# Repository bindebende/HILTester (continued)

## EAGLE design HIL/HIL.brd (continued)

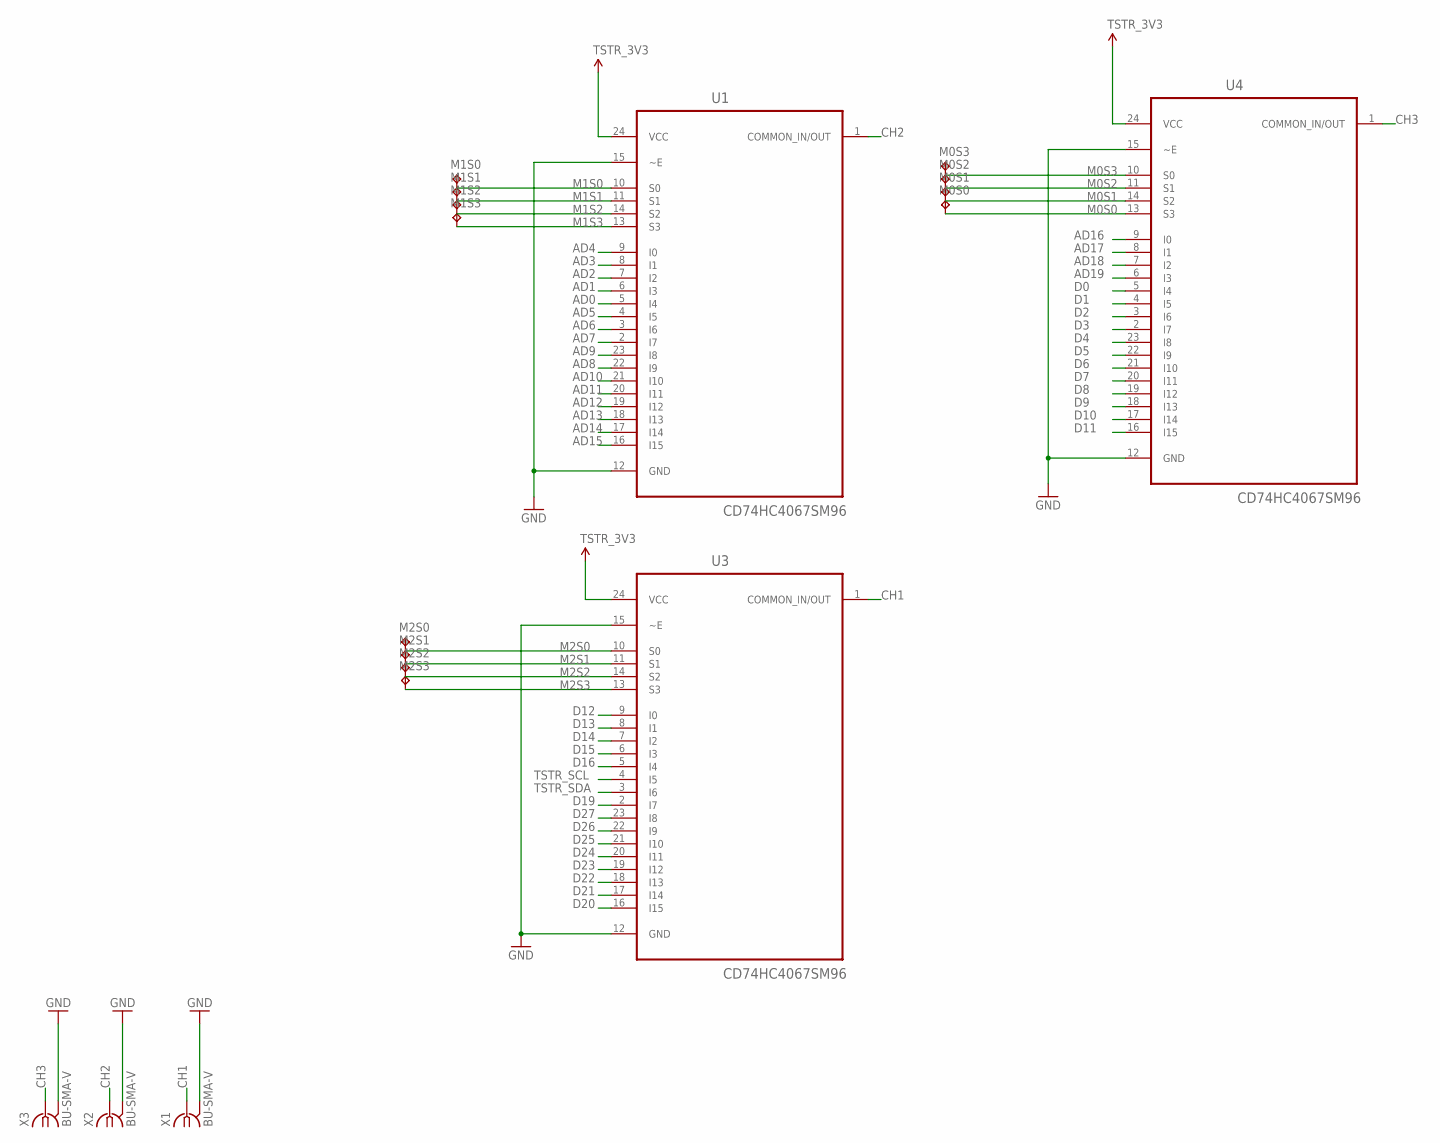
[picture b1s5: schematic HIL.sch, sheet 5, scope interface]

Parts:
M0S0, M0S1, M0S2, M0S3: TPB1,27; B1,27
M1S0, M1S1, M1S2, M1S3, M2S0, M2S1, M2S2, M2S3: M0S3; B1,27
U1, U3, U4: CD74HC4067SM96; SOP65P780X200-24N
X1, X2, X3: BU-SMA-V

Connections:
AD0: U1.5 (I4); also elsewhere on the board
AD1: U1.6 (I3); also elsewhere on the board
AD2: U1.7 (I2); also elsewhere on the board
AD3: U1.8 (I1); also elsewhere on the board
AD4: U1.9 (I0); also elsewhere on the board
AD5: U1.4 (I5); also elsewhere on the board
AD6: U1.3 (I6); also elsewhere on the board
AD7: U1.2 (I7); also elsewhere on the board
AD8: U1.22 (I9); also elsewhere on the board
AD9: U1.23 (I8); also elsewhere on the board
AD10: U1.21 (I10); also elsewhere on the board
AD11: U1.20 (I11); also elsewhere on the board
AD12: U1.19 (I12); also elsewhere on the board
AD13: U1.18 (I13); also elsewhere on the board
AD14: U1.17 (I14); also elsewhere on the board
AD15: U1.16 (I15); also elsewhere on the board
AD16: U4.9 (I0); also elsewhere on the board
AD17: U4.8 (I1); also elsewhere on the board
AD18: U4.7 (I2); also elsewhere on the board
AD19: U4.6 (I3); also elsewhere on the board
CH1: U3.1 (COMMON_IN/OUT), X1.1
CH2: U1.1 (COMMON_IN/OUT), X2.1
CH3: U4.1 (COMMON_IN/OUT), X3.1
D0: U4.5 (I4); also elsewhere on the board
D1: U4.4 (I5); also elsewhere on the board
D2: U4.3 (I6); also elsewhere on the board
D3: U4.2 (I7); also elsewhere on the board
D4: U4.23 (I8); also elsewhere on the board
D5: U4.22 (I9); also elsewhere on the board
D6: U4.21 (I10); also elsewhere on the board
D7: U4.20 (I11); also elsewhere on the board
D8: U4.19 (I12); also elsewhere on the board
D9: U4.18 (I13); also elsewhere on the board
D10: U4.17 (I14); also elsewhere on the board
D11: U4.16 (I15); also elsewhere on the board
D12: U3.9 (I0); also elsewhere on the board
D13: U3.8 (I1); also elsewhere on the board
D14: U3.7 (I2); also elsewhere on the board
D15: U3.6 (I3); also elsewhere on the board
D16: U3.5 (I4); also elsewhere on the board
D19: U3.2 (I7); also elsewhere on the board
D20: U3.16 (I15); also elsewhere on the board
D21: U3.17 (I14); also elsewhere on the board
D22: U3.18 (I13); also elsewhere on the board
D23: U3.19 (I12); also elsewhere on the board
D24: U3.20 (I11); also elsewhere on the board
D25: U3.21 (I10); also elsewhere on the board
D26: U3.22 (I9)
D27: U3.23 (I8)
GND: U1.12 (GND), U1.15 (~E), U3.12 (GND), U3.15 (~E), U4.12 (GND), U4.15 (~E), X1.2, X1.3 (2), X1.4 (2), X1.5 (2), X2.2, X2.3 (2), X2.4 (2), X2.5 (2), X3.2, X3.3 (2), X3.4 (2), X3.5 (2); also elsewhere on the board
M0S0: M0S0.TP, U4.13 (S3)
M0S1: M0S1.TP, U4.14 (S2)
M0S2: M0S2.TP, U4.11 (S1)
M0S3: M0S3.TP, U4.10 (S0)
M1S0: M1S0.TP, U1.10 (S0)
M1S1: M1S1.TP, U1.11 (S1)
M1S2: M1S2.TP, U1.14 (S2)
M1S3: M1S3.TP, U1.13 (S3)
M2S0: M2S0.TP, U3.10 (S0)
M2S1: M2S1.TP, U3.11 (S1)
M2S2: M2S2.TP, U3.14 (S2)
M2S3: M2S3.TP, U3.13 (S3)
TSTR_3V3: U1.24 (VCC), U3.24 (VCC), U4.24 (VCC); also elsewhere on the board
TSTR_SCL: U3.4 (I5); also elsewhere on the board
TSTR_SDA: U3.3 (I6); also elsewhere on the board

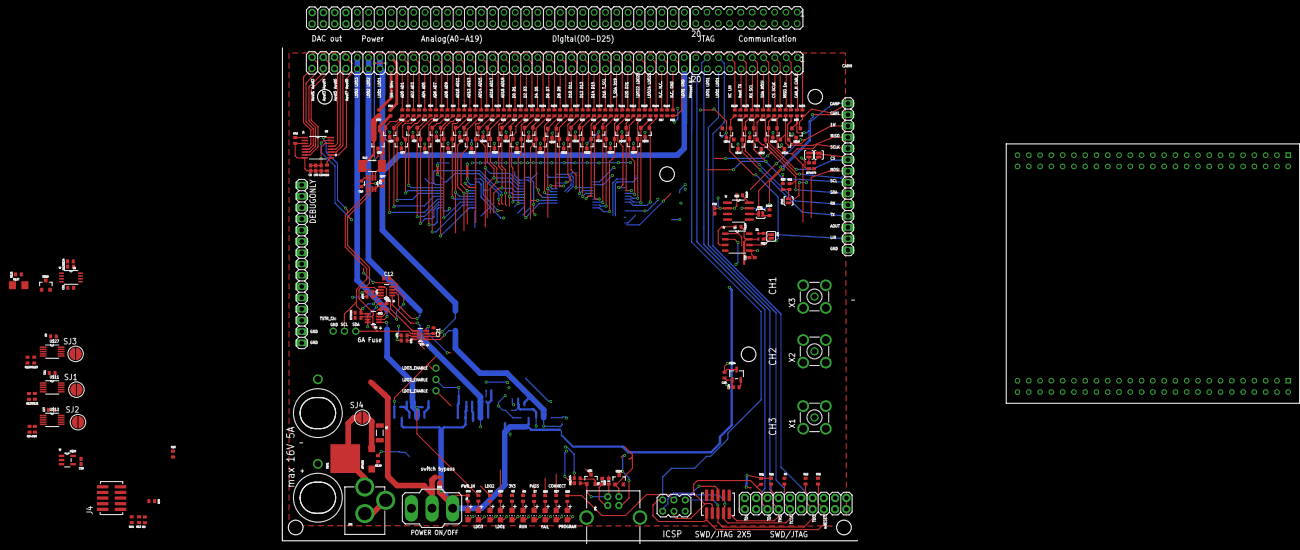
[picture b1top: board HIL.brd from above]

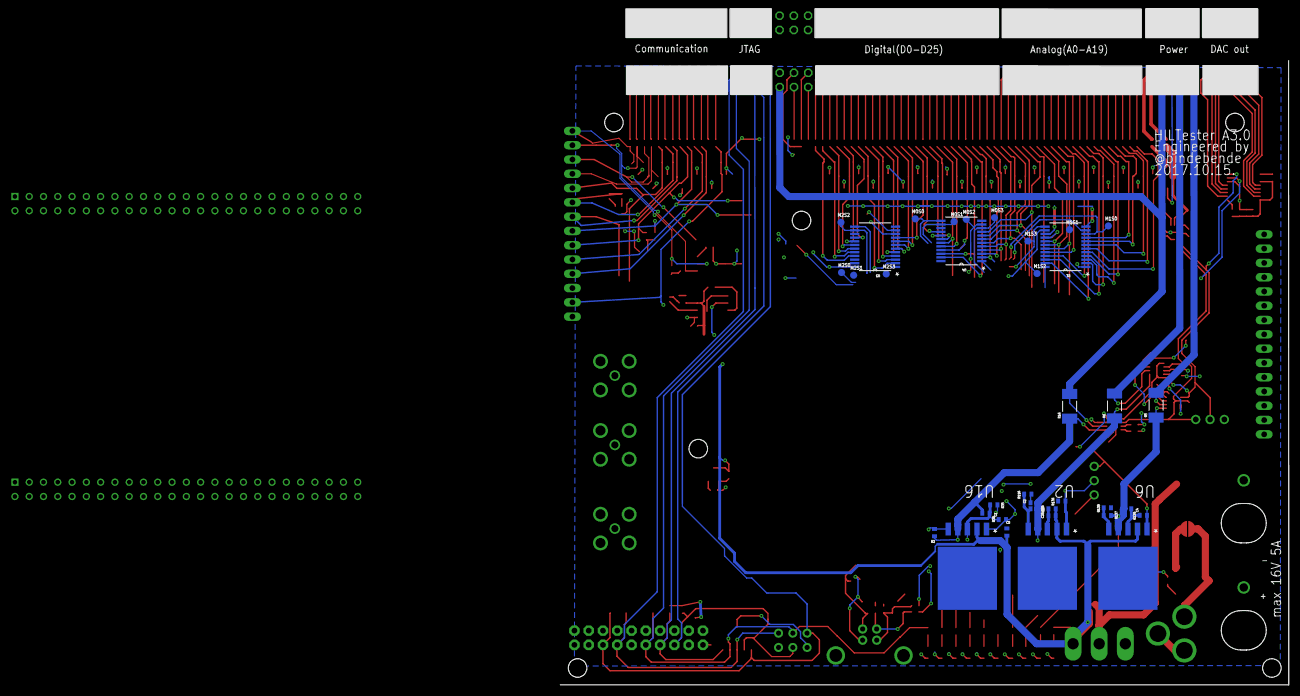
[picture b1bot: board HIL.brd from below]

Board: 2 copper layers, 129.5 x 111.0 mm, 269 parts (36 on the bottom side), 223 nets.

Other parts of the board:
STANDOFF1, STANDOFF5: STAND-OFF; STAND-OFF@1

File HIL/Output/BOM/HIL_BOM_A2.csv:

Qty;Value;Device;Package;Parts;Description
1;;320-916;320-916;S1;TOGGLE SWITCH
1;;DIODE-SOD523;SOD523;D1;DIODE
1;;GSH15;GSH15;F1;FUSE HOLDER
1;;JUMPER-2SMD-NC;SJ_2S;JP9;Jumper
1;;JUMPER-2SMD-NO;SJ_2S-NO;JP11;Jumper
10;;LEDCHIP-LED0805;CHIP-LED0805;LED1, LED2, LED3, LED4, LED5, LED6, LED7, LED8, LED9, LED10;LED
1;;MA10-2;MA10-2;SV1;PIN HEADER
1;;PINHD-1X14;1X14;JP3;PIN HEADER
1;;PINHD-1X15;1X15;DEBUGONLY;PIN HEADER
4;;PINHD-1X3CB;1X03-CLEANBIG;JP14, JP15, JP16, JP18;PIN HEADER
1;;PINHD-2X10;2X10;JP2;PIN HEADER
1;;PINHD-2X30;2X30;JP6;PIN HEADER
6;;R-EU_R0402;R0402;R2, R35, R37, R116, R137, R138;RESISTOR, European symbol
4;;R-US_R5025;R5025;R5, R6, R16, R17;RESISTOR, American symbol
4;0.1uF;C-EUC0402;C0402;C10, C12, C21, C22;CAPACITOR, European symbol
9;0.1uF;C-EUC0402K;C0402K;C3, C6, C13, C14, C16, C17, C18, C19, C20;CAPACITOR, European symbol
1;0.1uF;CC0402;C0402;C37;CAPACITOR, European symbol
3;0R;R-EU_R0402;R0402;R41, R44, R88;RESISTOR, European symbol
1;100;R-EU_R0402;R0402;R24;RESISTOR, European symbol
10;100R;R-EU_R0402;R0402;R3, R7, R8, R26, R27, R28, R29, R30, R33, R40;RESISTOR, European symbol
1;10k;R-EU_R0402;R0402;R25;RESISTOR, European symbol
6;10uF;C-EUC0402;C0402;C1, C2, C4, C5, C25, C26;CAPACITOR, European symbol
1;10uF;C-EUC0402K;C0402K;C7;CAPACITOR, European symbol
1;120;R-EU_R0402;R0402;R140;RESISTOR, European symbol
2;12pF;C-EUC0402K;C0402K;C9, C36;CAPACITOR, European symbol
1;1M;R-EU_R0402;R0402;R20;RESISTOR, European symbol
1;1k;R-EU_R0402;R0402;R117;RESISTOR, European symbol
2;1uF;C-EUC0402;C0402;C23, C24;CAPACITOR, European symbol
1;2.2uF;C-EUC0402K;C0402K;C15;CAPACITOR, European symbol
64;200R;R-EU_R0402;R0402;R39, R42, R43, R45, R47, R48, R49, R50, R51, R52, R53, R54, R55, R56, R57, R58, R59, R60, R61, R62, R63, R64, R65, R66, R67, R68, R82, R83, R84, R85, R86, R87, R91, R92, R93, R94, R95, R96, R97, R98, R99, R100, R101, R102, R103, R104, R105, R106, R107, R108, R109, R110, R111, R112, R113, R114, R115, R129, R130, R131, R132, R133, R134, R135;RESISTOR, European symbol
2;22R;RESISTOR0402-RES;0402-RES;R1, R38;Resistor
1;2k;R-EU_R0402;R0402;R23;RESISTOR, European symbol
16;4.7k;R-EU_R0402;R0402;R9, R10, R13, R14, R15, R18, R19, R34, R46, R69, R70, R71, R78, R79, R80, R81;RESISTOR, European symbol
1;4.87k 1%;R-EU_R0402;R0402;R22;RESISTOR, European symbol
16;4k7;R-EU_R0402;R0402;R4, R11, R12, R31, R32, R36, R72, R73, R74, R75, R76, R77, R118, R119, R136, R139;RESISTOR, European symbol
1;51;R-EU_R0402;R0402;R21;RESISTOR, European symbol
3;A1944-50;A1944-50;A1944;X1, X2, X4;BNC CONNECTOR 50 Ohm
1;ADUM1201ARZ;ADUM1201ARZ;SOIC127P600X175-8N;U14;Dual-Channel Digital Isolators
1;AVRISP-6;AVRISP-6;AVRISP;ISP1;AVR ISP HEADER
2;BINDING_POST;BINDING_POST;BINDING_POST;JP12, JP13;Single Banana jack.
3;CD74HC4067SM96;CD74HC4067SM96;SOP65P780X200-24N;U1, U3, U4;16-Channel Analog Multiplexer/Demultiplexer
2;DUT_CS_MASTER;JUMPER-2SMD-NO;SJ_2S-NO;JP4, JP10;Jumper
1;DUT_CS_RecieveAllMSG;JUMPER-2SMD-NO;SJ_2S-NO;JP7;Jumper
1;FT230XS;FT230XS;SOP63P600X175-16N;U17;I/F, USB2.0 FS TO BASIC UART
4;INA219AIDCNR;INA219AIDCNR;SOT65P280X145-8N;U9, U10, U11, U12;CURRENT/POWER MONITOR
2;JTAG_ARM_10PIN;JTAG_ARM_10PIN;CON_2X5_50MIL;J1, J4;
8;M0S3;TPB1,27;B1,27;M1S0, M1S1, M1S2, M1S3, M2S0, M2S1, M2S2, M2S3;Test pad
1;MCP1703T-3302E/CB;MCP1703T-3302E/CB;SOT95P300X145-3N;U$34;Low Quiescent Current LDO Regulator
1;MCP2003-E/SN;MCP2003-E/SN;SOIC127P600X175-8N;U7;LIN J2602 Transceiver,SOIC-8
1;MCP4725A0T-E/CH;MCP4725A0T-E/CH;SOT95P270X145-6N;U5;12-Bit Digital-to-Analog Converter with EEPROM
1;NX3225GA;NX3225GA;NDK3.2X2.5;Y3;
1;POWER_JACKPTH;POWER_JACKPTH;POWER_JACK_PTH;JP5;Power Jack
1;RESET;JUMPER-2SMD-NO;SJ_2S-NO;JP1;Jumper
1;SN65HVD230D;SN65HVD230D;SOIC127P600X175-8N;U15;3.3-V CAN TRANSCEIVERS
4;STAND-OFF;STAND-OFF;STAND-OFF;STANDOFF2, STANDOFF3, STANDOFF4, STANDOFF6;#4 Stand Off
1;SWS003;SWS003;SMS-003;S3;SMD Dip Switch 3 pol.
3;TL1963AKTTR.;TL1963AKTTR.;TO170P1485X457-6N;U2, U6, U16;LDO, REG, 1.5A, 1.21V TO 20V ADJ, 5TO263
1;TM4C1294NCPDT;TM4C1294NCPDT;TQFP128;U13;ARM MICROCONTROLLER
4;TPB1,27;TPB1,27;B1,27;M0S0, M0S1, M0S2, M0S3;Test pad
1;USB-B;USBPTH;USB-B-PTH;JP8;USB Connectors
33;zener_3.3V;MMBZ27VCLT1;SOT23-3;U$1, U$2, U$3, U$4, U$5, U$6, U$7, U$8, U$9, U$10, U$13, U$14, U$15, U$16, U$17, U$18, U$19, U$20, U$21, U$22, U$23, U$24, U$25, U$26, U$36, U$37, U$44, U$45, U$46, U$47, U$48, U$49, U$50;40W Zener-diode transient voltage suppressor (ESD protection)

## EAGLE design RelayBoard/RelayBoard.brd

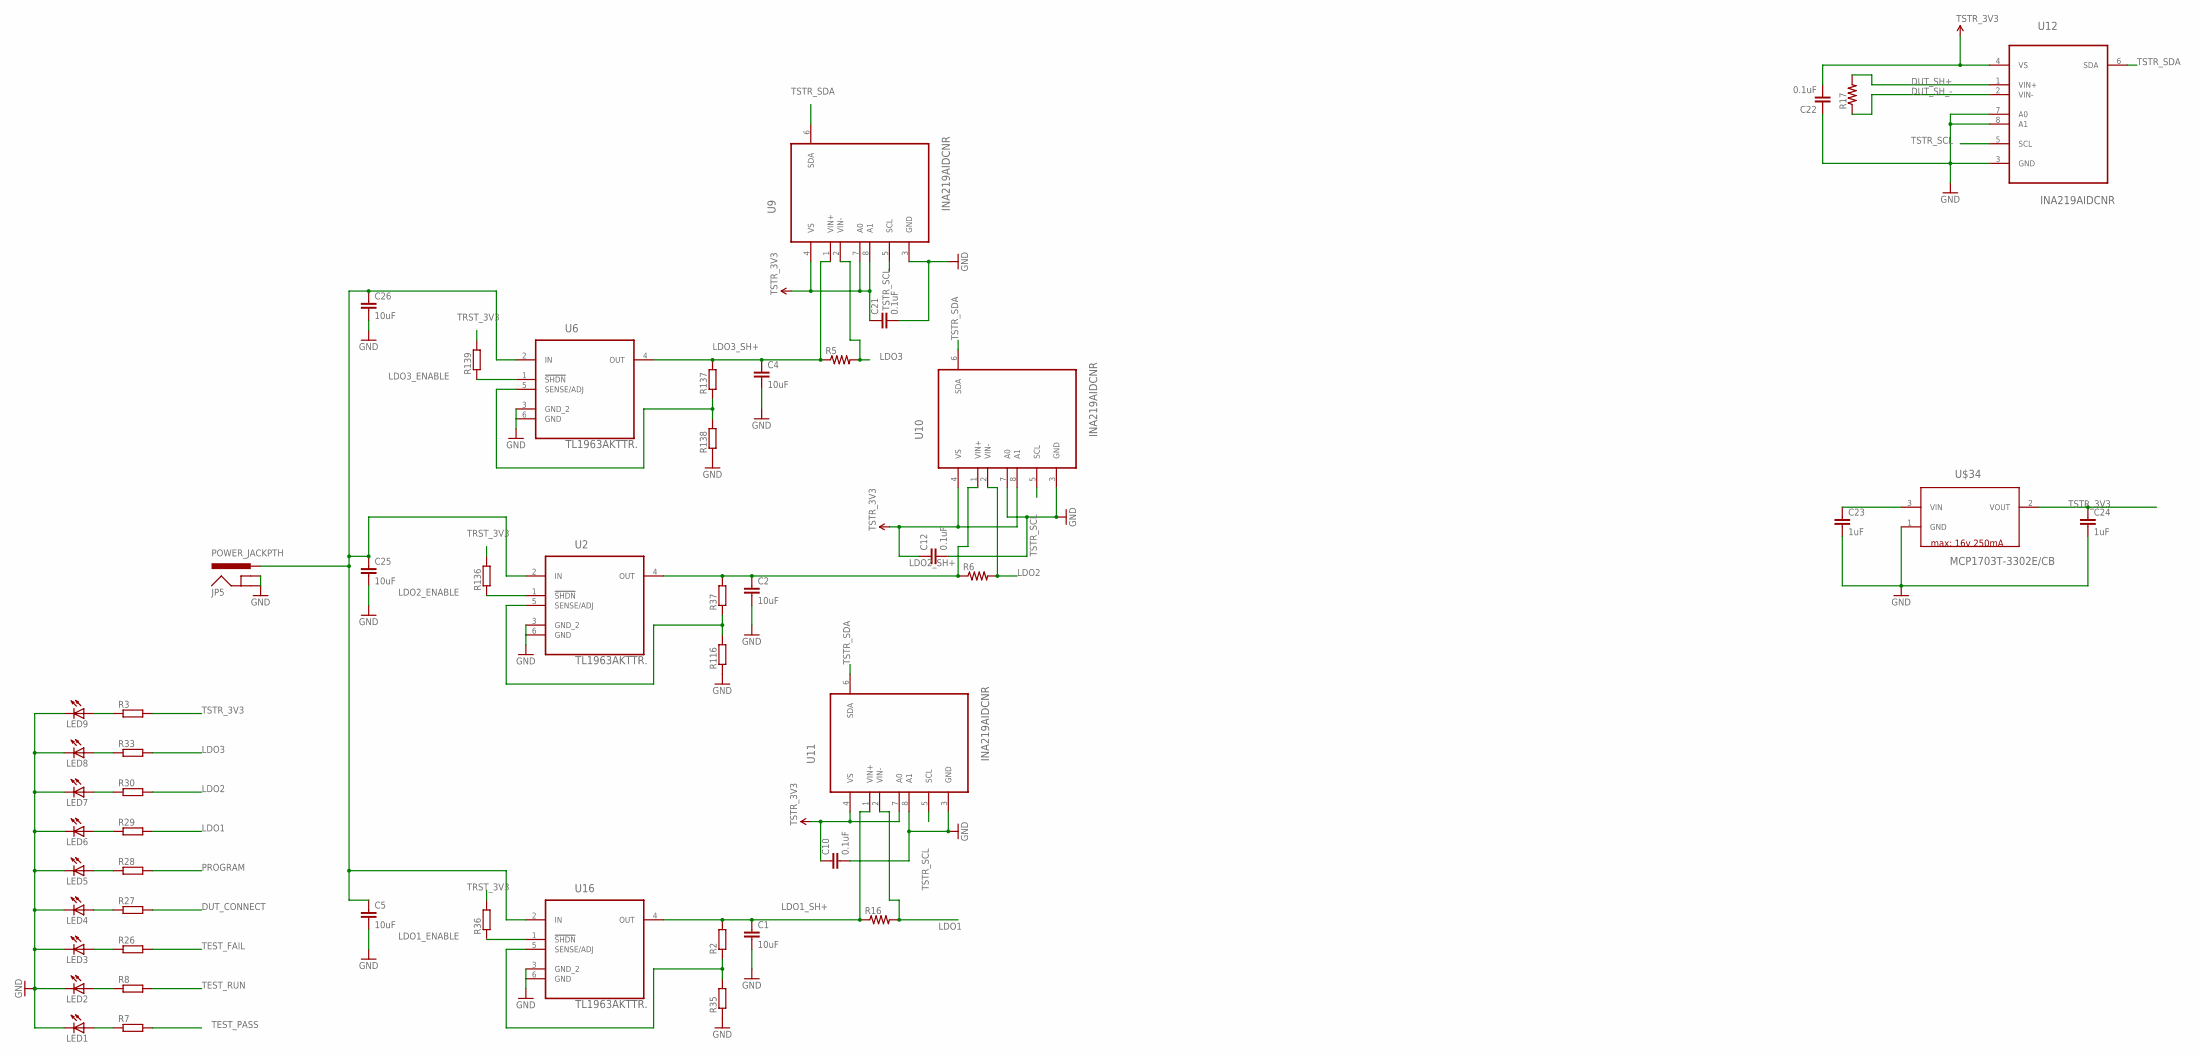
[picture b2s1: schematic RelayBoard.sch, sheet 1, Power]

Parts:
C1, C2, C4, C5, C25, C26: 10uF; C0402
C10, C12, C21, C22: 0.1uF; C0402
C23, C24: 1uF; C0402
JP5: POWER_JACKPTH; POWER_JACK_PTH
LED1, LED2, LED3, LED4, LED5, LED6, LED7, LED8, LED9: LEDCHIP-LED0805; CHIP-LED0805
R2, R3, R7, R8, R26, R27, R28, R29, R30, R33, R35, R36, R37, R116, R136, R137, R138, R139: R-EU_R0402; R0402
R5, R6, R16, R17: R-US_R5025; R5025
U2, U6, U16: TL1963AKTTR.; TO170P1485X457-6N
U9, U10, U11, U12: INA219AIDCNR; SOT65P280X145-8N
U$34: MCP1703T-3302E/CB; SOT95P300X145-3N

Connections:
ADJ3: R2.1, R35.2, U16.5 (SENSE/ADJ)
ADJ4: R37.1, R116.2, U2.5 (SENSE/ADJ)
ADJ5: R137.1, R138.2, U6.5 (SENSE/ADJ)
DUT_CONNECT: R27.2
DUT_SH+: R17.2, U12.1 (VIN+)
DUT_SH_-: R17.1, U12.2 (VIN-)
GND: C1.2, C2.2, C4.2, C5.2, C10.2, C12.2, C21.2, C22.1, C23.2, C24.2, C25.2, C26.2, JP5.GND, JP5.GNDBREAK, LED1.C, LED2.C, LED3.C, LED4.C, LED5.C, LED6.C, LED7.C, LED8.C, LED9.C, R35.1, R116.1, R138.1, U2.3 (GND_2), U2.6 (GND), U6.3 (GND_2), U6.6 (GND), U9.3 (GND), U10.3 (GND), U10.7 (A0), U11.3 (GND), U11.8 (A1), U12.3 (GND), U12.7 (A0), U12.8 (A1), U16.3 (GND_2), U16.6 (GND), U$34.1 (GND); also elsewhere on the board
LDO1: R16.2, R29.2, U11.2 (VIN-); also elsewhere on the board
LDO1_ENABLE: R36.1, U16.1 (!SHDN)
LDO1_SH+: C1.1, R2.2, R16.1, U11.1 (VIN+), U16.4 (OUT)
LDO2: R6.2, R30.2, U10.2 (VIN-); also elsewhere on the board
LDO2_ENABLE: R136.1, U2.1 (!SHDN)
LDO2_SH+: C2.1, R6.1, R37.2, U2.4 (OUT), U10.1 (VIN+)
LDO3: R5.2, R33.2, U9.2 (VIN-); also elsewhere on the board
LDO3_ENABLE: R139.1, U6.1 (!SHDN)
LDO3_SH+: C4.1, R5.1, R137.2, U6.4 (OUT), U9.1 (VIN+)
unnamed: LED2.A, R8.1
unnamed: LED1.A, R7.1
unnamed: LED3.A, R26.1
unnamed: LED4.A, R27.1
unnamed: LED5.A, R28.1
unnamed: LED6.A, R29.1
unnamed: LED7.A, R30.1
unnamed: LED8.A, R33.1
unnamed: LED9.A, R3.1
unnamed: C23.1, U$34.3 (VIN)
POWER_IN: C5.1, C25.1, C26.1, JP5.PWR, U2.2 (IN), U6.2 (IN), U16.2 (IN)
PROGRAM: R28.2
TEST_FAIL: R26.2
TEST_PASS: R7.2
TEST_RUN: R8.2
TRST_3V3: R36.2, R136.2, R139.2
TSTR_3V3: C10.1, C12.1, C21.1, C22.2, C24.1, R3.2, U9.4 (VS), U9.7 (A0), U9.8 (A1), U10.4 (VS), U10.8 (A1), U11.4 (VS), U11.7 (A0), U12.4 (VS), U$34.2 (VOUT); also elsewhere on the board
TSTR_SCL: U9.5 (SCL), U10.5 (SCL), U11.5 (SCL), U12.5 (SCL)
TSTR_SDA: U9.6 (SDA), U10.6 (SDA), U11.6 (SDA), U12.6 (SDA)

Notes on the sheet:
max: 16v 250mA

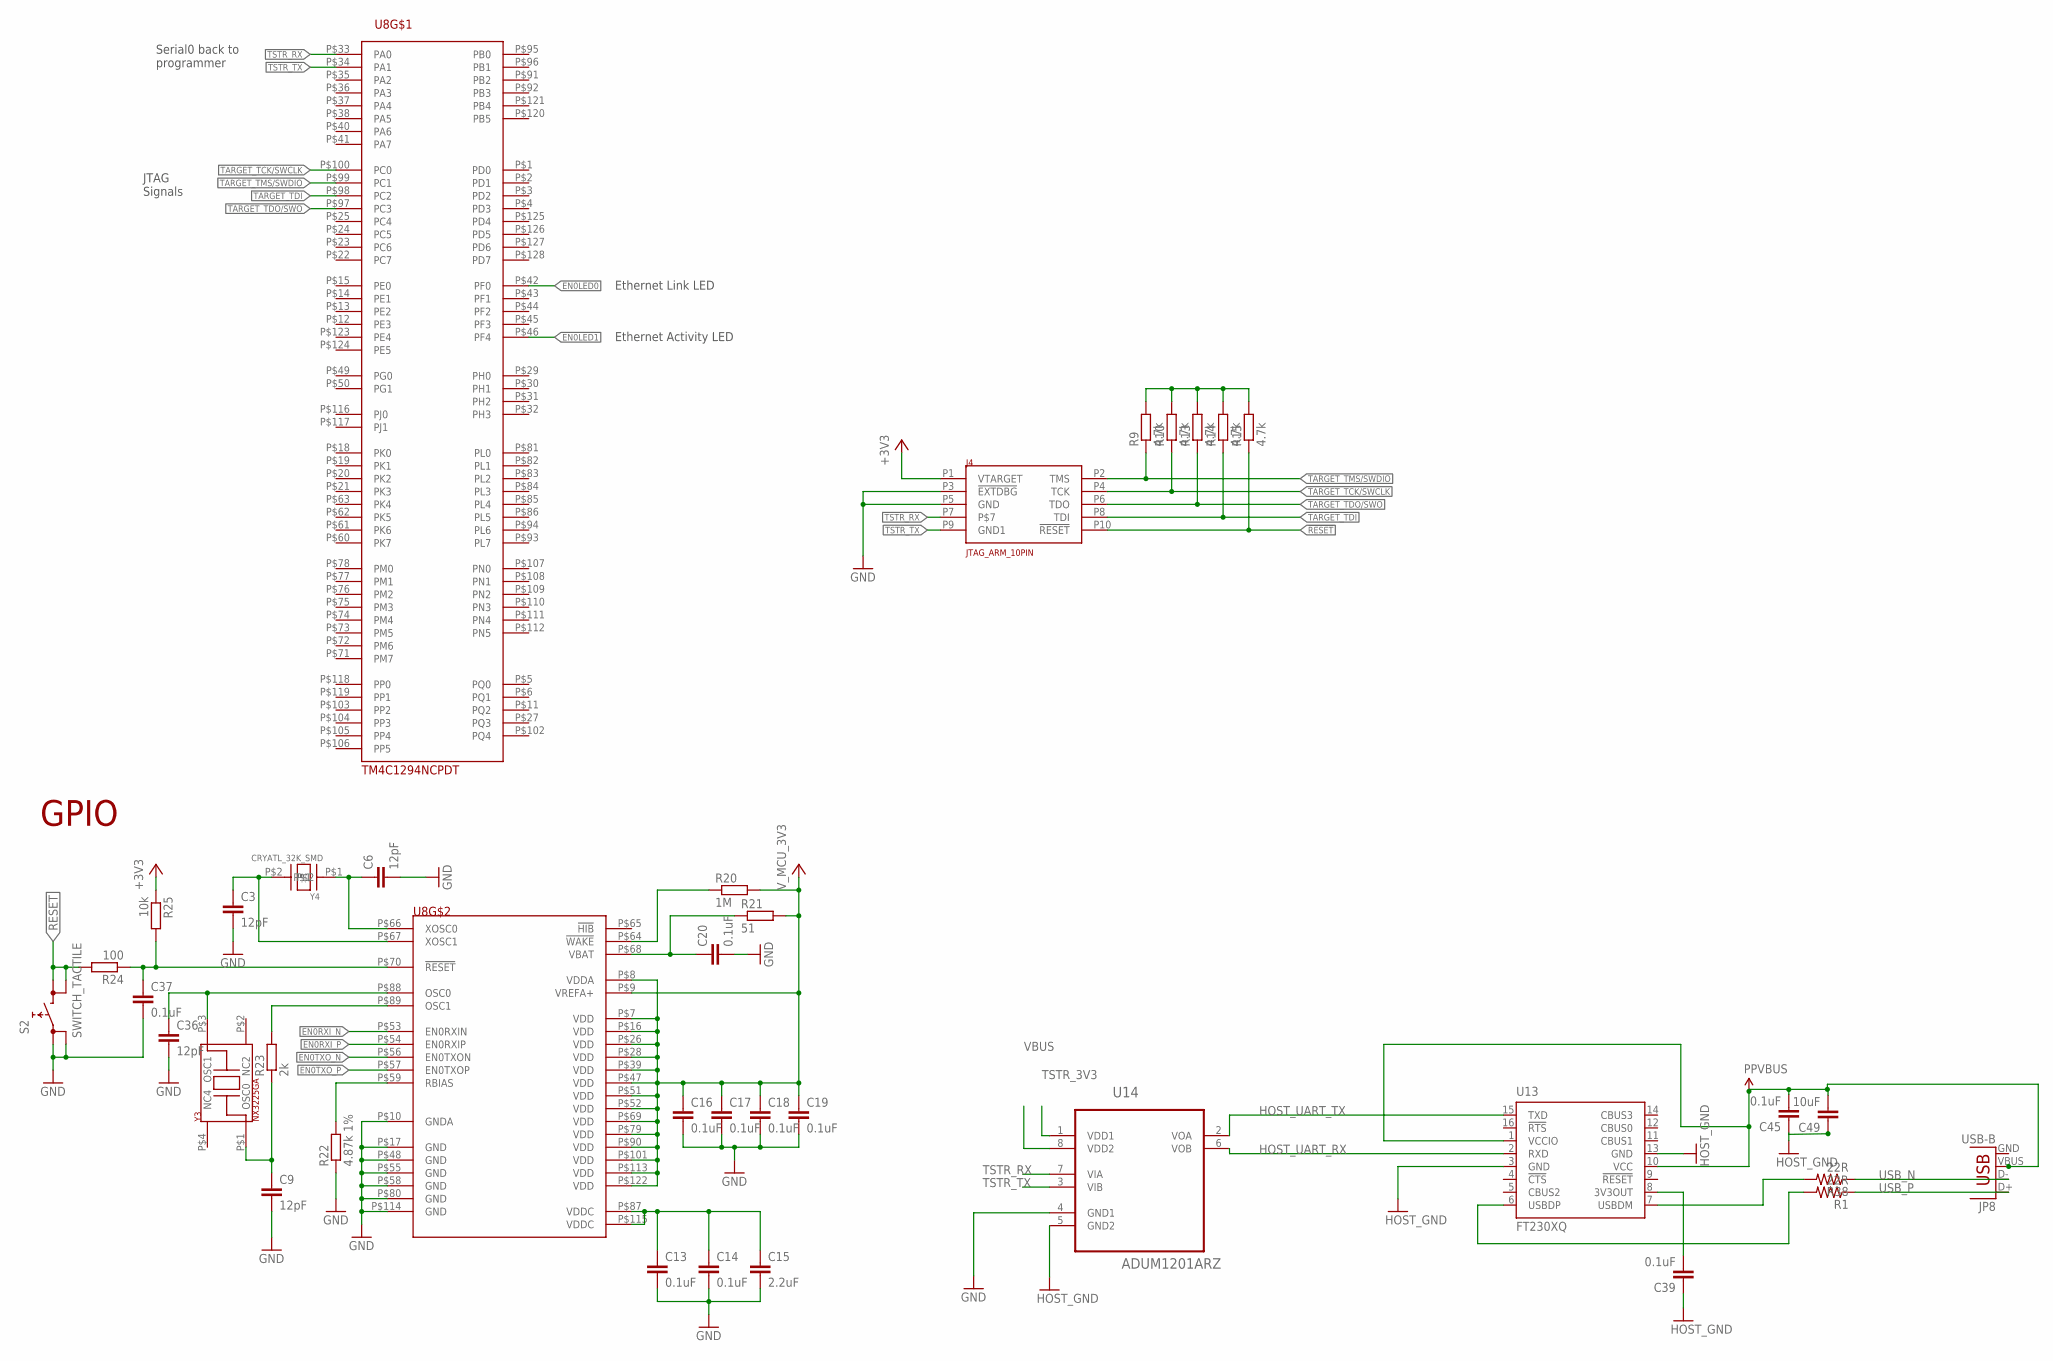
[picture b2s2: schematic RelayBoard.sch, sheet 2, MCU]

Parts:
C3, C6, C9, C36: 12pF; C0402K
C13, C14, C16, C17, C18, C19, C20: 0.1uF; C0402K
C15: 2.2uF; C0402K
C37, C39, C45: 0.1uF; C0402
C49: 10uF; C0402
J4: JTAG_ARM_10PIN; CON_2X5_50MIL
JP8: USB-B; USB-B-PTH
R1, R38: 22R; 0402-RES
R9, R10, R13, R14, R15: 4.7k; R0402
R20: 1M; R0402
R21: 51; R0402
R22: 4.87k 1%; R0402
R23: 2k; R0402
R24: 100; R0402
R25: 10k; R0402
S2: SWITCH_TACTILE; SWITCH_6MM_6MM_TE_CON_SMD
U8: TM4C1294NCPDT; TQFP-128
U13: FT230XQ; QFN16
U14: ADUM1201ARZ; SOIC127P600X175-8N
Y3: NX3225GA; NDK3.2X2.5
Y4: CRYATL_32K_SMD; CRYSTAL_32K_SMD

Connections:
!RESET: J4.P10 (!RESET), R15.1, R24.2, S2.P$3 (1), S2.P$4 (1)
EN0LED0: U8.P$42 (PF0)
EN0LED1: U8.P$46 (PF4)
EN0RXI_N: U8.P$53 (EN0RXIN)
EN0RXI_P: U8.P$54 (EN0RXIP)
EN0TXO_N: U8.P$56 (EN0TXON)
EN0TXO_P: U8.P$57 (EN0TXOP)
GND: C3.2, C6.2, C9.2, C13.2, C14.2, C15.2, C16.2, C17.2, C18.2, C19.2, C20.2, C36.2, C37.2, J4.P3 (!EXTDBG), J4.P5 (GND), R22.1, S2.P$1 (0), S2.P$2 (0), U8.P$10 (GNDA), U8.P$17 (GND), U8.P$48 (GND), U8.P$55 (GND), U8.P$58 (GND), U8.P$80 (GND), U8.P$114 (GND), U14.4 (GND1); also elsewhere on the board
HOST_GND: C39.1, C45.1, C49.1, U13.3 (GND), U13.13 (GND), U14.5 (GND2)
HOST_UART_RX: U13.2 (RXD), U14.6 (VOB)
HOST_UART_TX: U13.15 (TXD), U14.2 (VOA)
unnamed: R9.2, R10.2, R13.2, R14.2, R15.2
unnamed: C39.2, U13.8 (3V3OUT)
N_$2: C20.1, R21.1, U8.P$68 (VBAT)
N_$24: R20.1, U8.P$64 (!WAKE)
N_$28: C13.1, C14.1, C15.1, U8.P$87 (VDDC), U8.P$115 (VDDC)
N_$29: R22.2, U8.P$59 (RBIAS)
N_$30: R23.2, U8.P$89 (OSC1)
N_$31: C36.1, U8.P$88 (OSC0), Y3.P$3 (OSC1)
N_$32: C9.1, R23.1, Y3.P$1 (OSC0)
N_$33: C37.1, R24.1, R25.2, U8.P$70 (!RESET)
N_$34: C6.1, U8.P$66 (XOSC0), Y4.P$1
N_$35: C3.1, U8.P$67 (XOSC1), Y4.P$2
TARGET_TCK/SWCLK: J4.P4 (TCK), R10.1, U8.P$100 (PC0)
TARGET_TDI: J4.P8 (TDI), R14.1, U8.P$98 (PC2)
TARGET_TDO/SWO: J4.P6 (TDO), R13.1, U8.P$97 (PC3)
TARGET_TMS/SWDIO: J4.P2 (TMS), R9.1, U8.P$99 (PC1)
TSTR_3V3: C16.1, C17.1, C18.1, C19.1, J4.P1 (VTARGET), R20.2, R21.2, R25.1, U8.P$7 (VDD), U8.P$8 (VDDA), U8.P$9 (VREFA+), U8.P$16 (VDD), U8.P$26 (VDD), U8.P$28 (VDD), U8.P$39 (VDD), U8.P$47 (VDD), U8.P$51 (VDD), U8.P$52 (VDD), U8.P$69 (VDD), U8.P$79 (VDD), U8.P$90 (VDD), U8.P$101 (VDD), U8.P$113 (VDD), U8.P$122 (VDD), U14.1 (VDD1); also elsewhere on the board
TSTR_RX: J4.P7, U8.P$33 (PA0), U14.7 (VIA); also elsewhere on the board
TSTR_TX: J4.P9 (GND1), U8.P$34 (PA1), U14.3 (VIB); also elsewhere on the board
USBD_N: R38.2, U13.7 (USBDM)
USBD_P: R1.2, U13.6 (USBDP)
USB_N: JP8.D-, R38.1
USB_P: JP8.D+, R1.1
VBUS: C45.2, C49.2, JP8.VBUS, U13.1 (VCCIO), U13.10 (VCC), U14.8 (VDD2)

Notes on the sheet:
GPIO
Serial0 back to programmer
JTAG Signals
Ethernet Link LED
Ethernet Activity LED

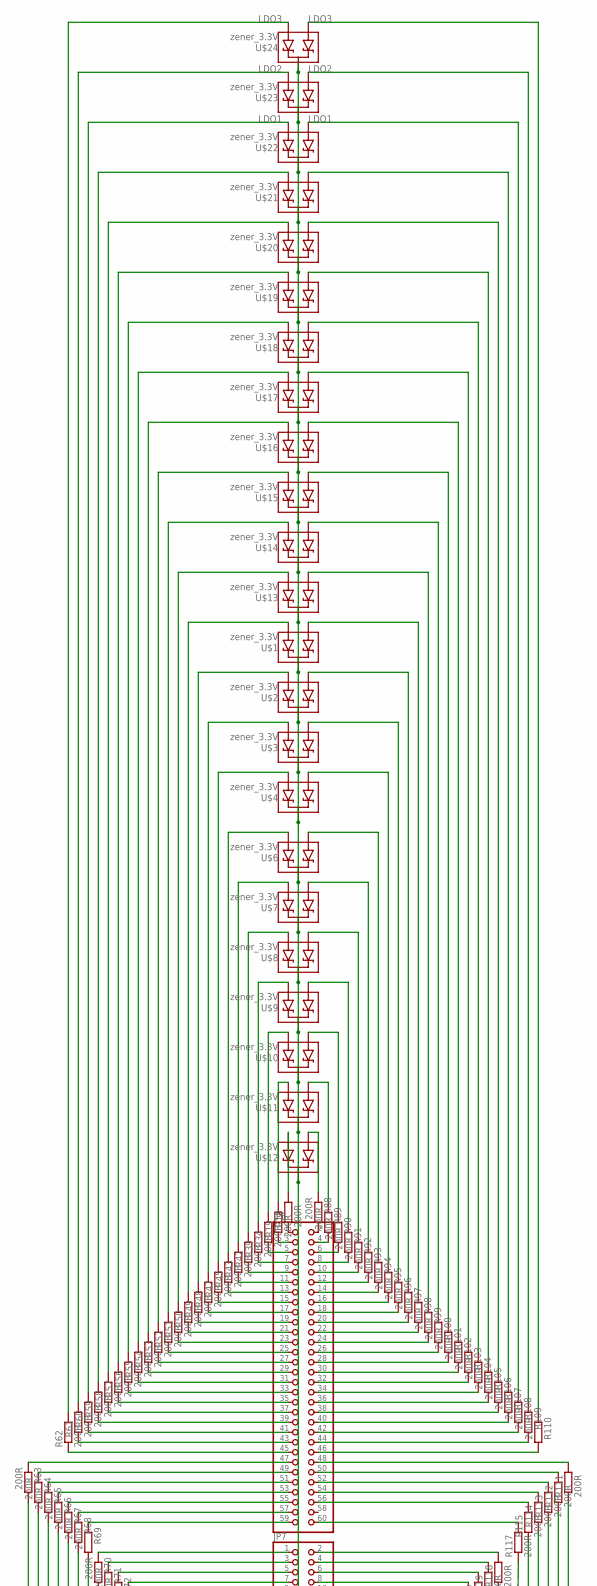
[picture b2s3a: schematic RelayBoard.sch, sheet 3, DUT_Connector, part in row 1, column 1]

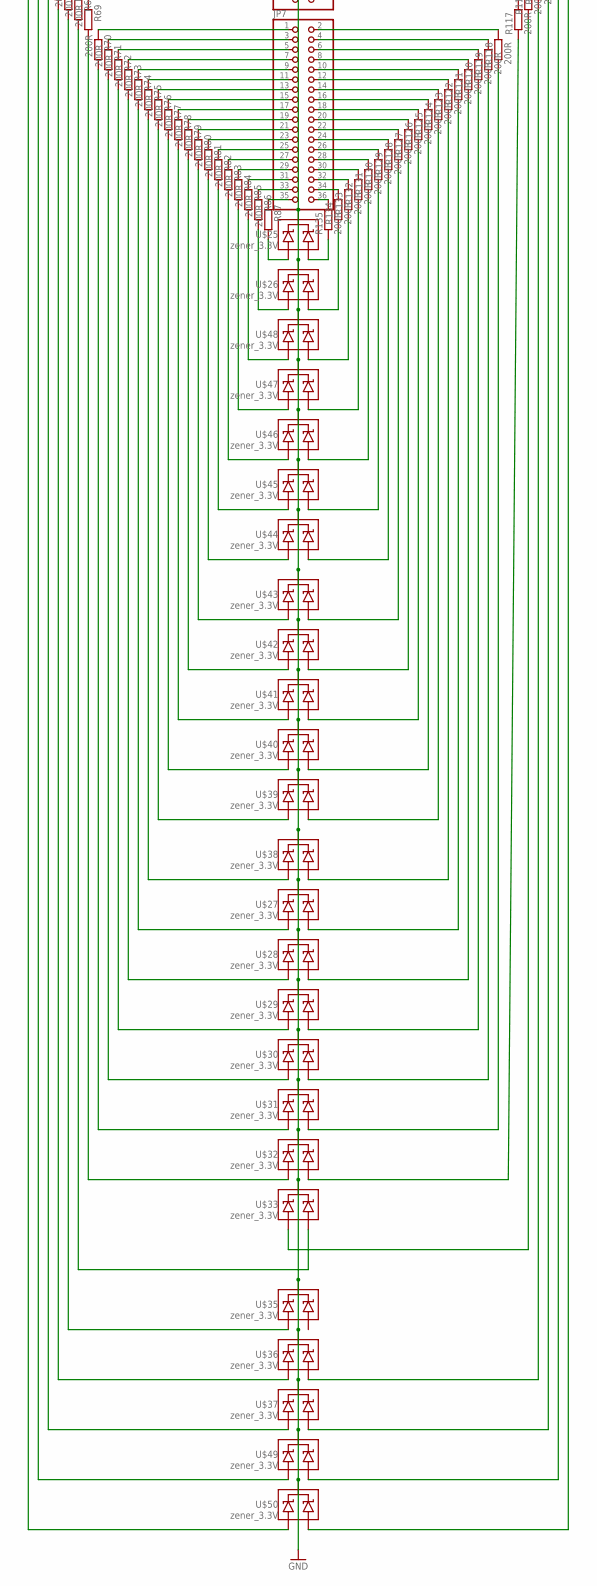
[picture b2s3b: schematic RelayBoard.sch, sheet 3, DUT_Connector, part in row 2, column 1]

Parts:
JP6: PINHD-2X30; 2X30
JP7: PINHD-2X18; 2X18
R18, R19, R34, R39, R42, R43, R45, R47, R48, R49, R50, R51, R52, R53, R54, R55, R56, R57, R58, R59, R60, R61, R62, R63, R64, R65, R66, R67, R68, R69, R70, R71, R72, R73, R74, R75, R76, R77, R78, R79, R80, R81, R82, R83, R84, R85, R86, R87, R88, R89, R90, R91, R92, R93, R94, R95, R96, R97, R98, R99, R100, R101, R102, R103, R104, R105, R106, R107, R108, R109, R110, R111, R112, R113, R114, R115, R117, R118, R119, R120, R121, R122, R123, R124, R125, R126, R127, R128, R129, R130, R131, R132, R133, R134, R135: 200R; R0402
U$1, U$2, U$3, U$4, U$6, U$7, U$8, U$9, U$10, U$11, U$12, U$13, U$14, U$15, U$16, U$17, U$18, U$19, U$20, U$21, U$22, U$23, U$24, U$25, U$26, U$27, U$28, U$29, U$30, U$31, U$32, U$33, U$35, U$36, U$37, U$38, U$39, U$40, U$41, U$42, U$43, U$44, U$45, U$46, U$47, U$48, U$49, U$50: zener_3.3V; SOT23-3

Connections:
GND: U$1.3 (C), U$2.3 (C), U$3.3 (C), U$4.3 (C), U$6.3 (C), U$7.3 (C), U$8.3 (C), U$9.3 (C), U$10.3 (C), U$11.3 (C), U$12.3 (C), U$13.3 (C), U$14.3 (C), U$15.3 (C), U$16.3 (C), U$17.3 (C), U$18.3 (C), U$19.3 (C), U$20.3 (C), U$21.3 (C), U$22.3 (C), U$23.3 (C), U$24.3 (C), U$25.3 (C), U$26.3 (C), U$27.3 (C), U$28.3 (C), U$29.3 (C), U$30.3 (C), U$31.3 (C), U$32.3 (C), U$33.3 (C), U$35.3 (C), U$36.3 (C), U$37.3 (C), U$38.3 (C), U$39.3 (C), U$40.3 (C), U$41.3 (C), U$42.3 (C), U$43.3 (C), U$44.3 (C), U$45.3 (C), U$46.3 (C), U$47.3 (C), U$48.3 (C), U$49.3 (C), U$50.3 (C); also elsewhere on the board
LDO1: R60.2, R108.1, U$22.1 (A1), U$22.2 (A2); also elsewhere on the board
LDO2: R61.2, R109.1, U$23.1 (A1), U$23.2 (A2); also elsewhere on the board
LDO3: R62.2, R110.1, U$24.1 (A1), U$24.2 (A2); also elsewhere on the board
unnamed: JP6.1, R18.1
unnamed: JP6.3, R19.1
unnamed: JP6.5, R34.1
unnamed: JP6.7, R39.1
unnamed: JP6.9, R42.1
unnamed: JP6.11, R43.1
unnamed: JP6.13, R45.1
unnamed: JP6.15, R47.1
unnamed: JP6.17, R48.1
unnamed: JP6.19, R49.1
unnamed: JP6.21, R50.1
unnamed: JP6.23, R51.1
unnamed: JP6.25, R52.1
unnamed: JP6.27, R53.1
unnamed: JP6.29, R54.1
unnamed: JP6.31, R55.1
unnamed: JP6.33, R56.1
unnamed: JP6.35, R57.1
unnamed: JP6.37, R58.1
unnamed: JP6.39, R59.1
unnamed: JP6.41, R60.1
unnamed: JP6.43, R61.1
unnamed: JP6.45, R62.1
unnamed: JP6.47, R63.1
unnamed: JP6.49, R64.1
unnamed: JP6.51, R65.1
unnamed: JP6.53, R66.1
unnamed: JP6.55, R67.1
unnamed: JP6.57, R68.1
unnamed: JP6.59, R69.1
unnamed: JP7.1, R70.1
unnamed: JP7.3, R71.1
unnamed: JP7.5, R72.1
unnamed: JP7.7, R73.1
unnamed: JP7.9, R74.1
unnamed: JP7.11, R75.1
unnamed: JP7.13, R76.1
unnamed: JP7.15, R77.1
unnamed: JP7.17, R78.1
unnamed: JP7.19, R79.1
unnamed: JP7.21, R80.1
unnamed: JP7.23, R81.1
unnamed: JP7.25, R82.1
unnamed: JP7.27, R83.1
unnamed: JP7.29, R84.1
unnamed: JP7.31, R85.1
unnamed: JP7.33, R86.1
unnamed: JP7.35, R87.1
unnamed: JP7.2, R118.2
unnamed: JP7.4, R119.2
unnamed: JP7.6, R120.2
unnamed: JP7.8, R121.2
unnamed: JP7.10, R122.2
unnamed: JP7.12, R123.2
unnamed: JP7.14, R124.2
unnamed: JP7.16, R125.2
unnamed: JP7.18, R126.2
unnamed: JP7.20, R127.2
unnamed: JP7.22, R128.2
unnamed: JP7.24, R129.2
unnamed: JP7.26, R130.2
unnamed: JP7.28, R131.2
unnamed: JP7.30, R132.2
unnamed: JP7.32, R133.2
unnamed: JP7.34, R134.2
unnamed: JP7.36, R135.2
unnamed: JP6.2, R88.2
unnamed: JP6.4, R89.2
unnamed: JP6.6, R90.2
unnamed: JP6.8, R91.2
unnamed: JP6.10, R92.2
unnamed: JP6.12, R93.2
unnamed: JP6.14, R94.2
unnamed: JP6.16, R95.2
unnamed: JP6.18, R96.2
unnamed: JP6.20, R97.2
unnamed: JP6.22, R98.2
unnamed: JP6.24, R99.2
unnamed: JP6.26, R100.2
unnamed: JP6.28, R101.2
unnamed: JP6.30, R102.2
unnamed: JP6.32, R103.2
unnamed: JP6.34, R104.2
unnamed: JP6.36, R105.2
unnamed: JP6.38, R106.2
unnamed: JP6.40, R107.2
unnamed: JP6.42, R108.2
unnamed: JP6.44, R109.2
unnamed: JP6.46, R110.2
unnamed: JP6.48, R111.2
unnamed: JP6.50, R112.2
unnamed: JP6.52, R113.2
unnamed: JP6.54, R114.2
unnamed: JP6.56, R115.2
unnamed: JP6.60, R117.2
unnamed: R18.2, U$12.2 (A2)
unnamed: R87.2, U$25.2 (A2)
unnamed: R88.1, U$12.1 (A1)
unnamed: R89.1, U$11.1 (A1)
unnamed: R19.2, U$11.2 (A2)
unnamed: R90.1, U$10.1 (A1)
unnamed: R34.2, U$10.2 (A2)
unnamed: R91.1, U$9.1 (A1)
unnamed: R39.2, U$9.2 (A2)
unnamed: R92.1, U$8.1 (A1)
unnamed: R42.2, U$8.2 (A2)
unnamed: R43.2, U$7.2 (A2)
unnamed: R93.1, U$7.1 (A1)
unnamed: R94.1, U$6.1 (A1)
unnamed: R45.2, U$6.2 (A2)
unnamed: R47.2, U$4.2 (A2)
unnamed: R95.1, U$4.1 (A1)
unnamed: R96.1, U$3.1 (A1)
unnamed: R48.2, U$3.2 (A2)
unnamed: R97.1, U$2.1 (A1)
unnamed: R49.2, U$2.2 (A2)
unnamed: R50.2, U$1.2 (A2)
unnamed: R98.1, U$1.1 (A1)
unnamed: R99.1, U$13.1 (A1)
unnamed: R51.2, U$13.2 (A2)
unnamed: R52.2, U$14.2 (A2)
unnamed: R100.1, U$14.1 (A1)
unnamed: R101.1, U$15.1 (A1)
unnamed: R53.2, U$15.2 (A2)
unnamed: R54.2, U$16.2 (A2)
unnamed: R102.1, U$16.1 (A1)
unnamed: R55.2, U$17.2 (A2)
unnamed: R103.1, U$17.1 (A1)
unnamed: R104.1, U$18.1 (A1)
unnamed: R56.2, U$18.2 (A2)
unnamed: R105.1, U$19.1 (A1)
unnamed: R57.2, U$19.2 (A2)
unnamed: R106.1, U$20.1 (A1)
unnamed: R58.2, U$20.2 (A2)
unnamed: R59.2, U$21.2 (A2)
unnamed: R107.1, U$21.1 (A1)
unnamed: R135.1, U$25.1 (A1)
unnamed: R134.1, U$26.1 (A1)
unnamed: R86.2, U$26.2 (A2)
unnamed: R85.2, U$48.2 (A2)
unnamed: R133.1, U$48.1 (A1)
unnamed: R84.2, U$47.2 (A2)
unnamed: R83.2, U$46.2 (A2)
unnamed: R82.2, U$45.2 (A2)
unnamed: R81.2, U$44.2 (A2)
unnamed: R80.2, U$43.2 (A2)
unnamed: R79.2, U$42.2 (A2)
unnamed: R78.2, U$41.2 (A2)
unnamed: R77.2, U$40.2 (A2)
unnamed: R76.2, U$39.2 (A2)
unnamed: R75.2, U$38.2 (A2)
unnamed: R73.2, U$28.2 (A2)
unnamed: R72.2, U$29.2 (A2)
unnamed: R71.2, U$30.2 (A2)
unnamed: R70.2, U$31.2 (A2)
unnamed: R69.2, U$32.2 (A2)
unnamed: R68.2, U$33.1 (A1)
unnamed: R67.2, U$35.2 (A2)
unnamed: R66.2, U$36.2 (A2)
unnamed: R129.1, U$44.1 (A1)
unnamed: R132.1, U$47.1 (A1)
unnamed: R131.1, U$46.1 (A1)
unnamed: R130.1, U$45.1 (A1)
unnamed: R74.2, U$27.2 (A2)
unnamed: R128.1, U$43.1 (A1)
unnamed: R127.1, U$42.1 (A1)
unnamed: R65.2, U$37.2 (A2)
unnamed: R64.2, U$49.2 (A2)
unnamed: R63.2, U$50.2 (A2)
unnamed: R126.1, U$41.1 (A1)
unnamed: R125.1, U$40.1 (A1)
unnamed: R124.1, U$39.1 (A1)
unnamed: R123.1, U$38.1 (A1)
unnamed: R122.1, U$27.1 (A1)
unnamed: R121.1, U$28.1 (A1)
unnamed: R120.1, U$29.1 (A1)
unnamed: R119.1, U$30.1 (A1)
unnamed: R118.1, U$31.1 (A1)
unnamed: R117.1, U$32.1 (A1)
unnamed: R115.1, U$33.2 (A2)
unnamed: R114.1, U$36.1 (A1)
unnamed: R113.1, U$37.1 (A1)
unnamed: R112.1, U$49.1 (A1)
unnamed: R111.1, U$50.1 (A1)
